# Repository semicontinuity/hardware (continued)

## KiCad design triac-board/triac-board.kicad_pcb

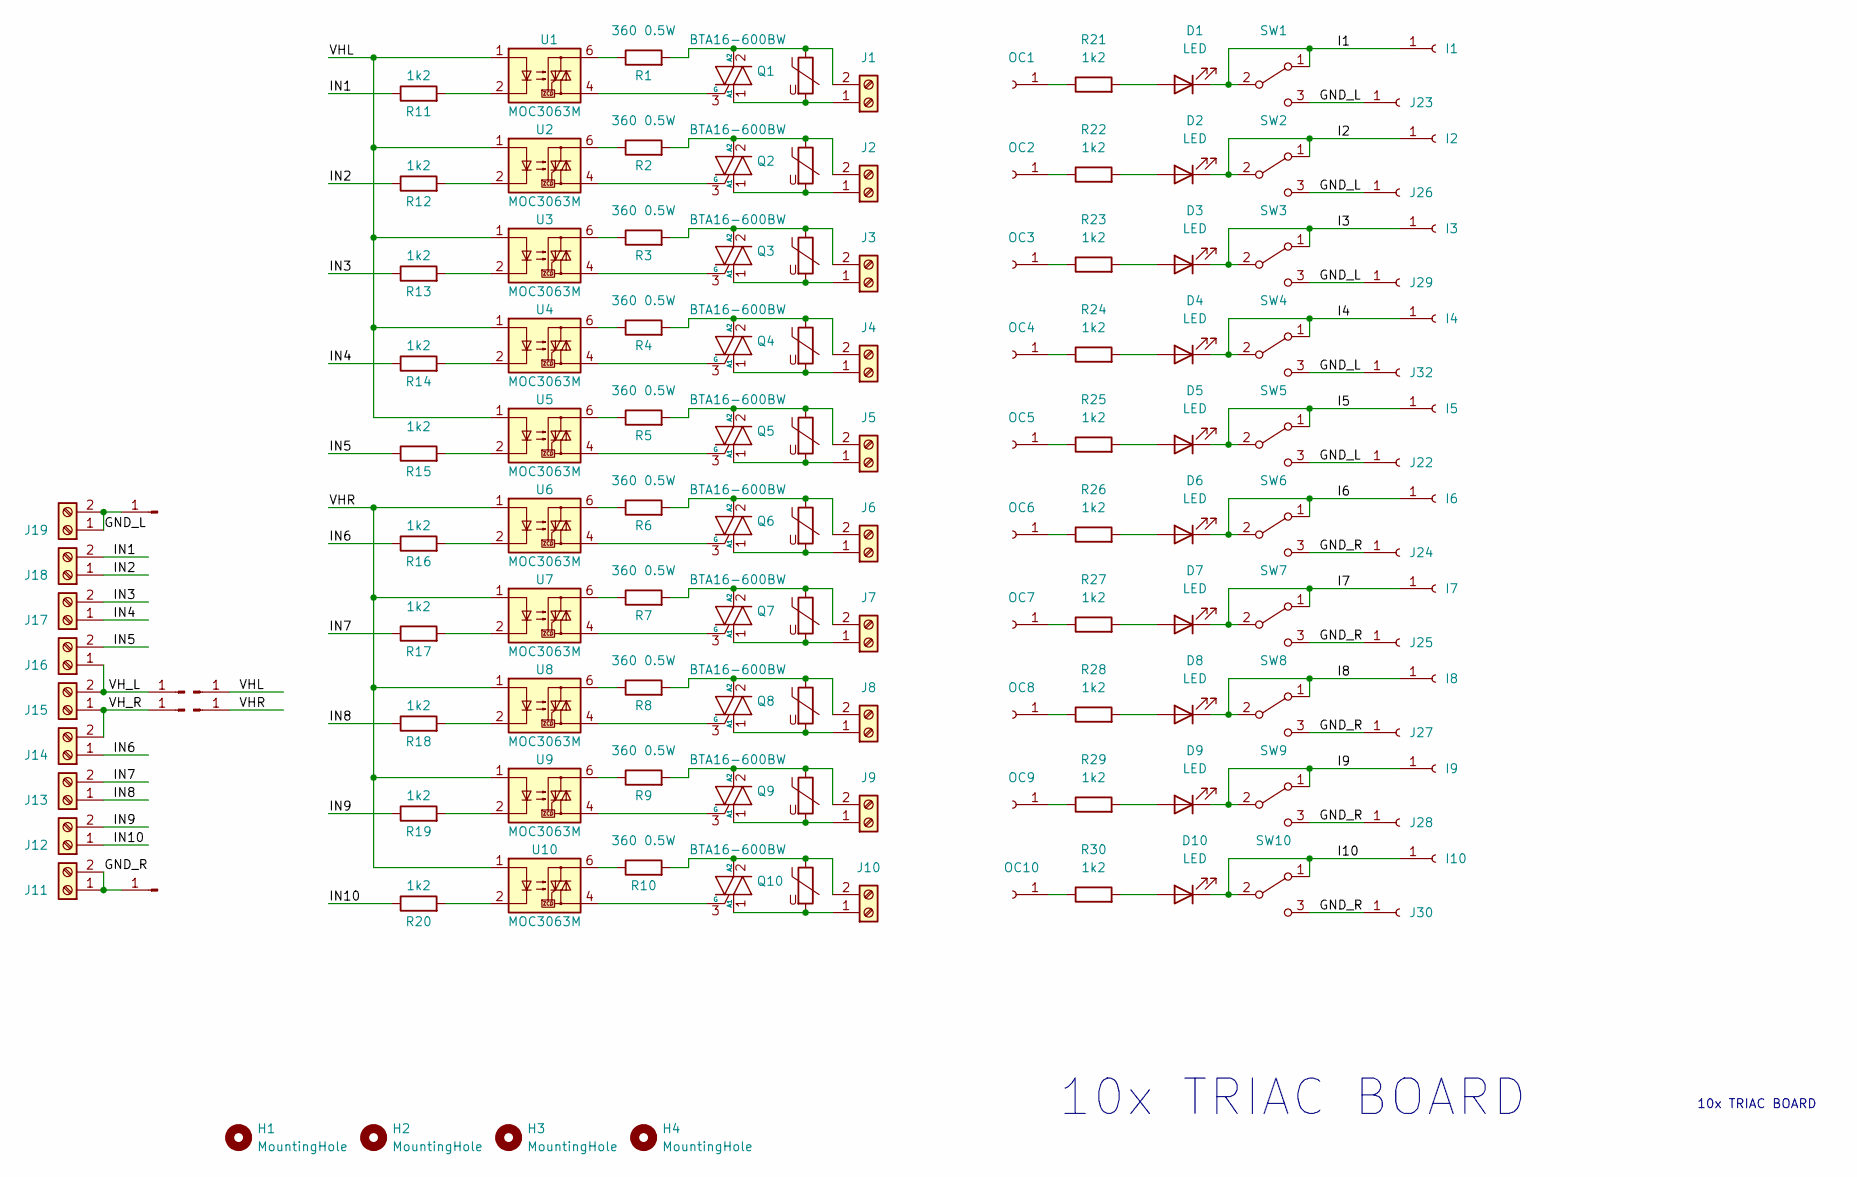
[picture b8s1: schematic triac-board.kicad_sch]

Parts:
D1, D2, D3, D4, D5, D6, D7, D8, D9, D10: LED; LED_D3.0mm
H1, H2, H3, H4: MountingHole; MountingHole_3.2mm_M3
I1, I2, I3, I4, I5, I6, I7, I8, I9, I10: Conn_01x01_Female; SolderWire-0.5sqmm_1x01_D0.9mm_OD2.3mm
J1, J2, J3, J4, J5, J6, J7, J8, J9, J10, J11, J12, J13, J14, J15, J16, J17, J18, J19: Screw_Terminal_01x02; TerminalBlock_Phoenix_MKDS-1,5-2_1x02_P5.00mm_Horizontal
J20, J21, J31, J33, J34, J35: Conn_01x01_Male; Pin_D1.3mm_L11.0mm
J22, J23, J24, J25, J26, J27, J28, J29, J30, J32: Conn_01x01_Female; SolderWire-0.5sqmm_1x01_D0.9mm_OD2.3mm
OC1, OC2, OC3, OC4, OC5, OC6, OC7, OC8, OC9, OC10: Conn_01x01_Female; SolderWire-0.5sqmm_1x01_D0.9mm_OD2.3mm
Q1, Q2, Q3, Q4, Q5, Q6, Q7, Q8, Q9, Q10: BTA16-600BW; TO-220-3_Vertical_Staggered
R1, R2, R3, R4, R5, R6, R7, R8, R9, R10: 360 0.5W; R_Axial_DIN0309_L9.0mm_D3.2mm_P20.32mm_Horizontal
R11, R12, R13, R14, R15, R16, R17, R18, R19, R20: 1k2; R_Axial_DIN0207_L6.3mm_D2.5mm_P10.16mm_Horizontal
R21, R22, R23, R24, R25, R26, R27, R28, R29, R30: 1k2; R_Axial_DIN0207_L6.3mm_D2.5mm_P7.62mm_Horizontal
RV1, RV2, RV3, RV4, RV5, RV6, RV7, RV8, RV9, RV10: 275V; RV_Disc_D9mm_W4.2mm_P5mm
SW1, SW2, SW3, SW4, SW5, SW6, SW7, SW8, SW9, SW10: SW_SPDT; PinHeader_1x03_P2.54mm_Vertical
U1, U2, U3, U4, U5, U6, U7, U8, U9, U10: MOC3063M; DIP-6_W7.62mm

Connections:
/GND_L: J19.1, J19.2, J20.1, J22.1, J23.1, J26.1, J29.1, J32.1, SW1.3 (C), SW2.3 (C), SW3.3 (C), SW4.3 (C), SW5.3 (C)
/GND_R: J11.1, J11.2, J21.1, J24.1, J25.1, J27.1, J28.1, J30.1, SW6.3 (C), SW7.3 (C), SW8.3 (C), SW9.3 (C), SW10.3 (C)
/I1: D1.1 (K), I1.1, SW1.1 (A), SW1.2 (B)
/I2: D2.1 (K), I2.1, SW2.1 (A), SW2.2 (B)
/I3: D3.1 (K), I3.1, SW3.1 (A), SW3.2 (B)
/I4: D4.1 (K), I4.1, SW4.1 (A), SW4.2 (B)
/I5: D5.1 (K), I5.1, SW5.1 (A), SW5.2 (B)
/I6: D6.1 (K), I6.1, SW6.1 (A), SW6.2 (B)
/I7: D7.1 (K), I7.1, SW7.1 (A), SW7.2 (B)
/I8: D8.1 (K), I8.1, SW8.1 (A), SW8.2 (B)
/I9: D9.1 (K), I9.1, SW9.1 (A), SW9.2 (B)
/I10: D10.1 (K), I10.1, SW10.1 (A), SW10.2 (B)
/IN1: J18.2, R11.1
/IN2: J18.1, R12.1
/IN3: J17.2, R13.1
/IN4: J17.1, R14.1
/IN5: J16.2, R15.1
/IN6: J14.1, R16.1
/IN7: J13.2, R17.1
/IN8: J13.1, R18.1
/IN9: J12.2, R19.1
/IN10: J12.1, R20.1
/VHL: J34.1, U1.1, U2.1, U3.1, U4.1, U5.1
/VHR: J35.1, U6.1, U7.1, U8.1, U9.1, U10.1
/VH_L: J15.2, J16.1, J31.1
/VH_R: J14.2, J15.1, J33.1
unnamed: D1.2 (A), R21.2
unnamed: D2.2 (A), R22.2
unnamed: D3.2 (A), R23.2
unnamed: D4.2 (A), R24.2
unnamed: D5.2 (A), R25.2
unnamed: D6.2 (A), R26.2
unnamed: D7.2 (A), R27.2
unnamed: D8.2 (A), R28.2
unnamed: D9.2 (A), R29.2
unnamed: D10.2 (A), R30.2
unnamed: J1.1, Q1.1 (A1), RV1.2
unnamed: J1.2, Q1.2 (A2), R1.2, RV1.1
unnamed: J2.1, Q2.1 (A1), RV2.2
unnamed: J2.2, Q2.2 (A2), R2.2, RV2.1
unnamed: J3.1, Q3.1 (A1), RV3.2
unnamed: J3.2, Q3.2 (A2), R3.2, RV3.1
unnamed: J4.1, Q4.1 (A1), RV4.2
unnamed: J4.2, Q4.2 (A2), R4.2, RV4.1
unnamed: J5.1, Q5.1 (A1), RV5.2
unnamed: J5.2, Q5.2 (A2), R5.2, RV5.1
unnamed: J6.1, Q6.1 (A1), RV6.2
unnamed: J6.2, Q6.2 (A2), R6.2, RV6.1
unnamed: J7.1, Q7.1 (A1), RV7.2
unnamed: J7.2, Q7.2 (A2), R7.2, RV7.1
unnamed: J8.1, Q8.1 (A1), RV8.2
unnamed: J8.2, Q8.2 (A2), R8.2, RV8.1
unnamed: J9.1, Q9.1 (A1), RV9.2
unnamed: J9.2, Q9.2 (A2), R9.2, RV9.1
unnamed: J10.1, Q10.1 (A1), RV10.2
unnamed: J10.2, Q10.2 (A2), R10.2, RV10.1
unnamed: OC1.1, R21.1
unnamed: OC2.1, R22.1
unnamed: OC3.1, R23.1
unnamed: OC4.1, R24.1
unnamed: OC5.1, R25.1
unnamed: OC6.1, R26.1
unnamed: OC7.1, R27.1
unnamed: OC8.1, R28.1
unnamed: OC9.1, R29.1
unnamed: OC10.1, R30.1
unnamed: Q1.3 (G), U1.4
unnamed: Q2.3 (G), U2.4
unnamed: Q3.3 (G), U3.4
unnamed: Q4.3 (G), U4.4
unnamed: Q5.3 (G), U5.4
unnamed: Q6.3 (G), U6.4
unnamed: Q7.3 (G), U7.4
unnamed: Q8.3 (G), U8.4
unnamed: Q9.3 (G), U9.4
unnamed: Q10.3 (G), U10.4
unnamed: R1.1, U1.6
unnamed: R2.1, U2.6
unnamed: R3.1, U3.6
unnamed: R4.1, U4.6
unnamed: R5.1, U5.6
unnamed: R6.1, U6.6
unnamed: R7.1, U7.6
unnamed: R8.1, U8.6
unnamed: R9.1, U9.6
unnamed: R10.1, U10.6
unnamed: R11.2, U1.2
unnamed: R12.2, U2.2
unnamed: R13.2, U3.2
unnamed: R14.2, U4.2
unnamed: R15.2, U5.2
unnamed: R16.2, U6.2
unnamed: R17.2, U7.2
unnamed: R18.2, U8.2
unnamed: R19.2, U9.2
unnamed: R20.2, U10.2

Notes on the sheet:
10x TRIAC BOARD

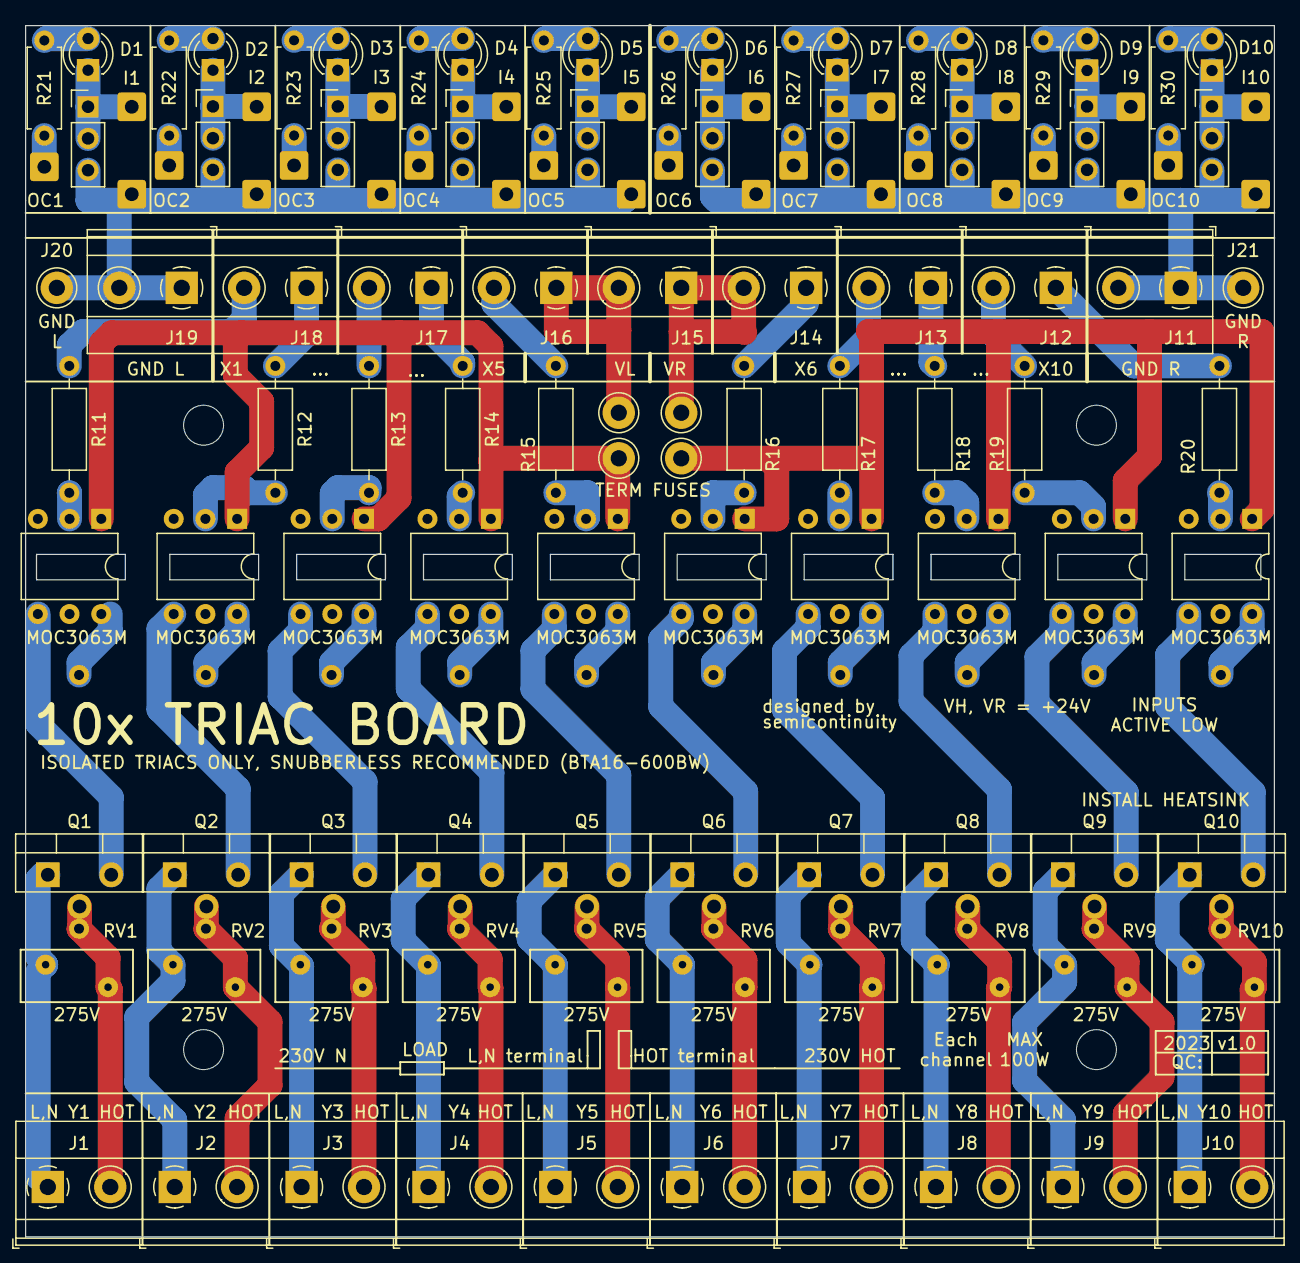
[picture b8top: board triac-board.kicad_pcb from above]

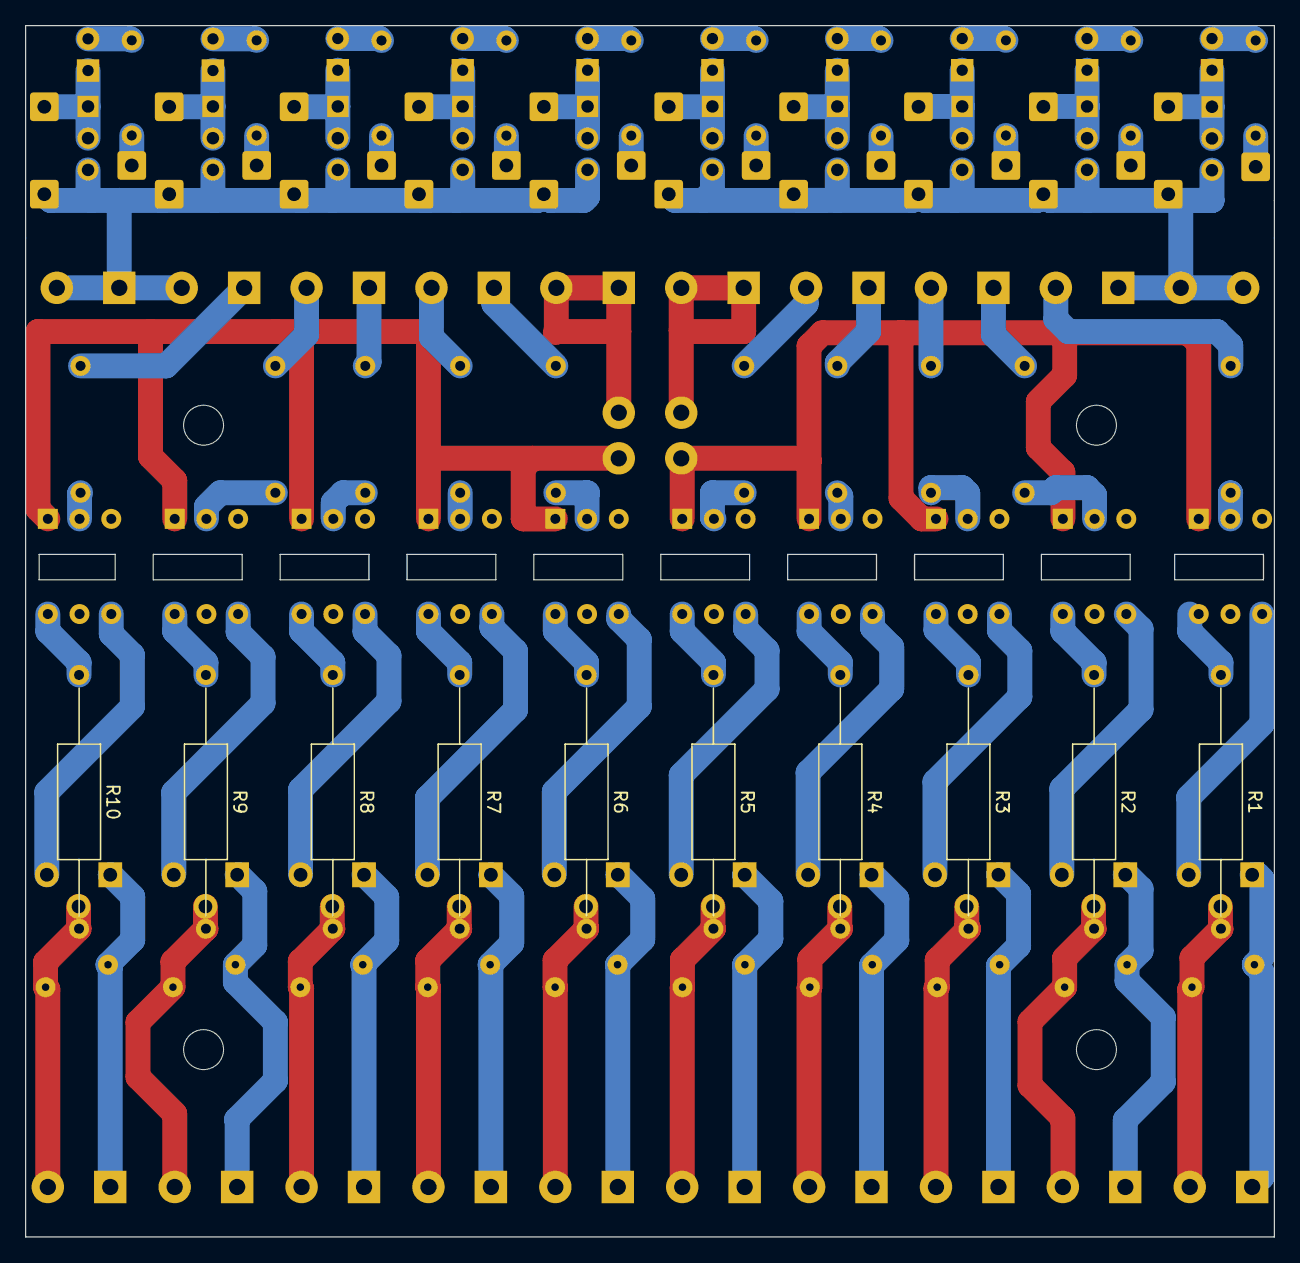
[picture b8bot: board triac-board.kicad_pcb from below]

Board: 2 copper layers, 100.0 x 97.0 mm, 139 parts (10 on the bottom side), 96 nets.

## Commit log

2012-07-04 added boards
2012-12-12 added segment_display_2x_static
2013-03-20 added rpi-can-rs485 board
2013-08-28 interim drop
2015-12-24 avr-fusebit-doctor-enhanced
2016-06-14 added stm32-board-adapter
2018-09-06 added rockchip-mics
2019-01-28 added avr-isp-adapter
2019-01-28 added breakout-4x-step-down
2019-01-28 added rpi-display-5110
2019-01-28 added esp8266-adapter
2019-01-28 added my-microchip-pot.lbr
2019-01-28 misc changes
2019-01-28 added tact-switches
2019-01-28 added nas-adapter-board
2019-03-15 eagle-libraries
2019-04-11 midi-in-out: initial schematics and placement
2019-06-03 cnc-spindle-driver
2019-06-19 added avr-fusebit-doctor-adapter-tqfp32
2019-06-19 midi-in-out edits
2019-07-19 case-bottom.scad
2019-07-22 added scad files
2019-07-30 cnc3018: added buttons board
2019-08-01 cnc3018: added arduino shield
2019-08-01 cnc3018: interim drop
2019-08-02 cnc3018 += spindle drivers
2019-08-08 added uart-opto-isolation
2019-09-09 cnc3018: changed buttons board + case
2019-09-09 cnc3018: plates g-code
2019-09-10 cnc3018: fill_rect g-code
2019-09-10 cnc3018: case for opto-isolation board
2019-09-10 cnc3018: fixed cases
2019-11-10 gcode.py: use class
2020-01-10 stm32-board-adapter enhancements
2020-03-04 cnc3018 updates
2020-03-04 added ac-dc-48V-10A
2020-04-14 cnc-controller hardware files
2020-05-25 cnc3018: case holes, front panel
2020-07-01 gcode.py enhancements
2020-08-01 cnc-controller mechanical
2020-10-06 added midi-in-out-mini
2020-12-22 added zebra labels
2020-12-22 cnc3018 update
2021-03-05 cnc-controller labels
2021-06-28 load board
2022-05-04 breakout-i2c-24c02
2022-05-06 breakout-ps2
2023-05-12 plastron plate
2023-05-14 triac-board
2023-05-30 plastron stub
2023-06-24 triac-board-r-top
2023-07-28 button-panel.kicad_pro
2023-07-29 triac-board-front
2024-01-22 far-servo-adapter initial commit
2024-01-23 far-servo-adapter += terminals
2024-03-28 din-3u-button-panel stub
2024-04-12 din-3u-button-panel: update
2024-04-13 din-3u-button-panel-top
2024-04-14 din-3u-button-panel
2024-04-14 button-panel
2024-05-13 wall_outlets_template
2025-04-20 led-panel.kicad
2025-11-20 toggle-switch-panel
2025-11-22 toggle-switch-panel-5x
